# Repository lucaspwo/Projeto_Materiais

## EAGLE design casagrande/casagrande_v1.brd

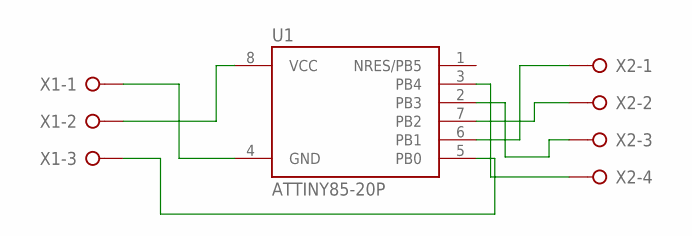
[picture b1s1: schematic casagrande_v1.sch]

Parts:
U1: ATTINY85-20P; PDIP08_300MIL
X1: W237-03P; W237-133
X2: W237-04P; W237-4P

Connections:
2: U1.7 (PB2), X2.2
3: U1.2 (PB3), X2.3
4: U1.3 (PB4), X2.4
BTN: U1.5 (PB0), X1.3
GND: U1.4 (GND), X1.1
unnamed: U1.6 (PB1), X2.1
VCC: U1.8 (VCC), X1.2

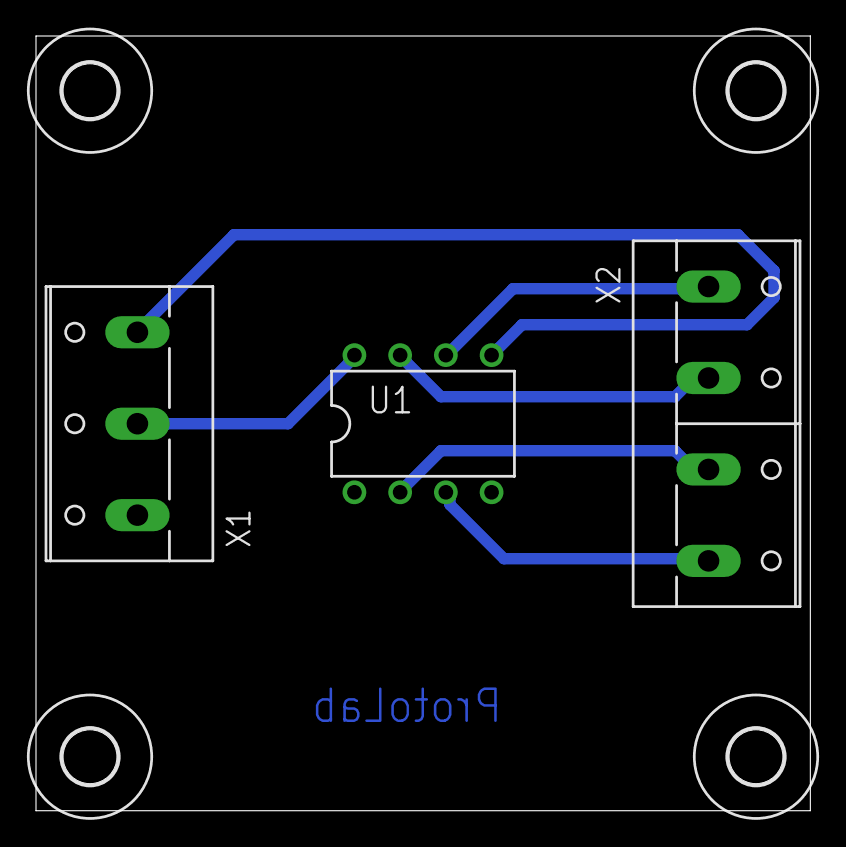
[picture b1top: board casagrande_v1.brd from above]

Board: 2 copper layers, 43.0 x 43.0 mm, 7 parts (0 on the bottom side), 7 nets.

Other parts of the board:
U$1, U$2, U$3, U$4: 3,0

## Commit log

2017-11-08 Primeiro commit
2018-01-31 Peq. Modificações
2018-05-20 Atual. 19/05/18
2018-05-25 Peq. atualização
2018-06-01 Versão RC1
2018-06-13 Placa controladora v1
